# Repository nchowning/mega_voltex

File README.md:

# MEGA Voltex
An Arduino Mega 2560 Sound Voltex controller shield for use with [ACreal_IO](https://github.com/Nadeflore/ACreal_IO).

This is still SUPER early days. The plan is to solder components to this shield, desolder the USB connector & power connector from an Arduino Mega 2560, slap this bad boy on top of it, and design a 3D printed enclosure for it.

# Credit
- [mon's PocketVoltex](https://github.com/mon/PocketVoltex) - Rotary encoder footprint & model. mon has a ton of amazing projects and is a super nice guy!
- [kcswalter's Electronic CAD libraries](http://smisioto.no-ip.org/elettronica/kicad/kicad-en.htm) - Arduino Mega header. Lots of useful libraries, footprints, & models here!
- [KiCad's footprints](https://github.com/KiCad/kicad-footprints) - I modified a couple of their SW_Cherry MX1A footprints to add LED through-holes. I plan on submitting a PR upstream for this.

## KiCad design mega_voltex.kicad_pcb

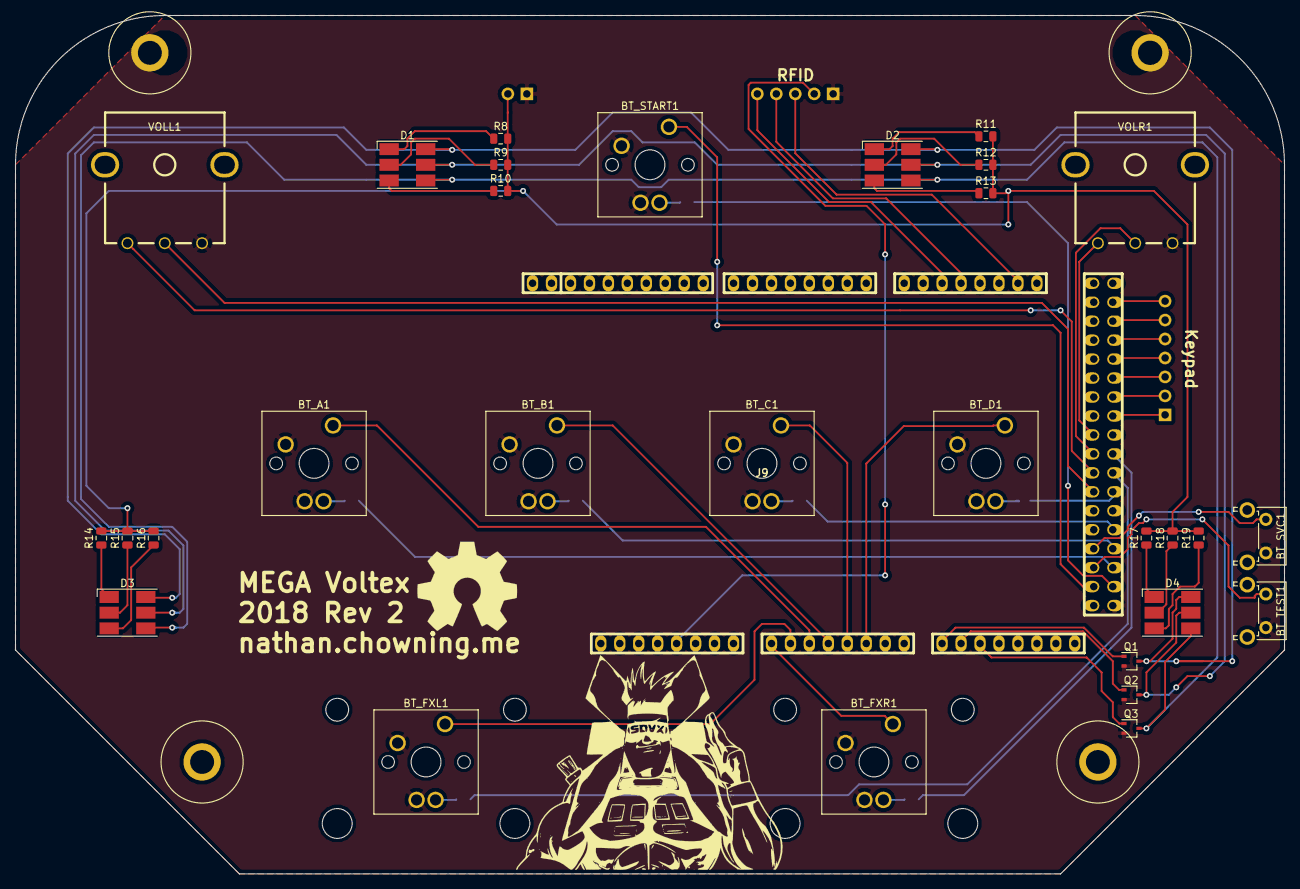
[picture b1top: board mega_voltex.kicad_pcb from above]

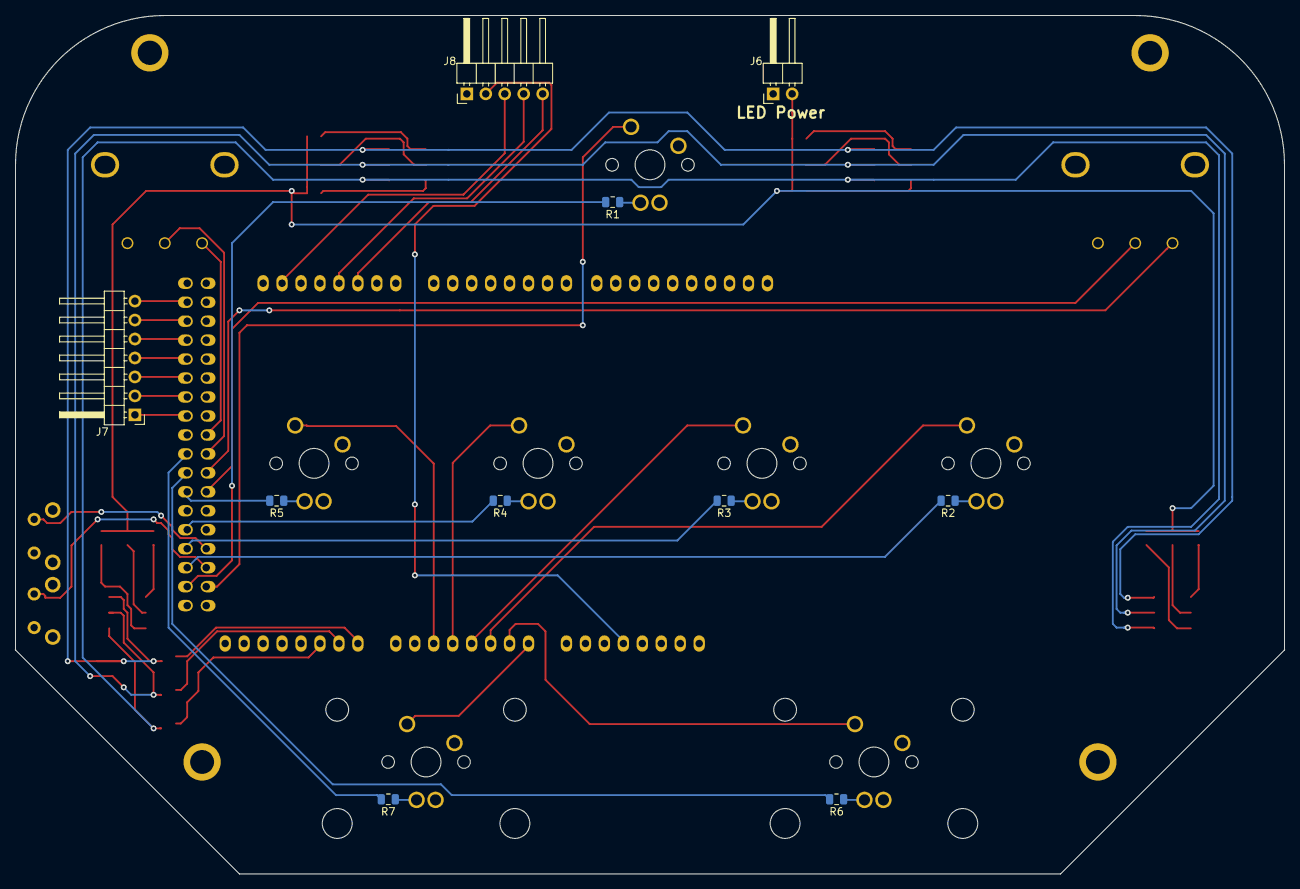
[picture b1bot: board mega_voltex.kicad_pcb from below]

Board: 2 copper layers, 170.0 x 115.0 mm, 44 parts (10 on the bottom side), 58 nets.

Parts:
BT_A1: SW_Push_LED; SW_Cherry_MX1A_1.00u_PCB
BT_B1: SW_Push_LED; SW_Cherry_MX1A_1.00u_PCB
BT_C1: SW_Push_LED; SW_Cherry_MX1A_1.00u_PCB
BT_D1: SW_Push_LED; SW_Cherry_MX1A_1.00u_PCB
BT_FXL1: SW_Push_LED; SW_Cherry_MX1A_2.00u_PCB
BT_FXR1: SW_Push_LED; SW_Cherry_MX1A_2.00u_PCB
BT_START1: SW_Push_LED; SW_Cherry_MX1A_1.00u_PCB
BT_SVC1: SW_Push; SW_Tactile_SPST_Angled_PTS645Vx58-2LFS
BT_TEST1: SW_Push; SW_Tactile_SPST_Angled_PTS645Vx58-2LFS
D1, D2, D3, D4: RGBLED_CREE_CLP6C; LED_RGB_Cree-PLCC-6_6x5mm_P2.1mm
J6: HEADER_2; PinHeader_1x02_P2.54mm_Horizontal
J7: HEADER_7; PinHeader_1x07_P2.54mm_Horizontal
J8: HEADER_5; PinHeader_1x05_P2.54mm_Horizontal
J9: Arduino_Mega_Header; arduino_mega_header
Mounting Hole: Banana_Jack_1Pin
Mounting Hole#2, Mounting Hole#3: Banana_Jack_1Pin
Q1, Q2, Q3: MMBT2222AWT1G; SOT-323_SC-70
R1, R2, R3, R4, R5, R6, R7, R8, R9, R10, R11, R12, R13, R14, R15, R16, R17, R18, R19: R_Small_US; R_0805_2012Metric
VOLL1: Rotary_Encoder; Encoder_Bourns_PEC16
VOLR1: Rotary_Encoder; Encoder_Bourns_PEC16

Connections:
5V: J8.2, J9.5
12V: J6.2, R8.2, R9.2, R10.2, R11.2, R12.2, R13.2, R14.2, R15.2, R16.2, R17.2, R18.2, R19.2
BT_A: BT_A1.1, J9.11
BT_B: BT_B1.1, J9.12
BT_C: BT_C1.1, J9.13
BT_D: BT_D1.1, J9.14
BT_FXL: BT_FXL1.1, J9.10
BT_FXR: BT_FXR1.1, J9.9
BT_START: BT_START1.1, J9.26
BT_SVC: BT_SVC1.1, J9.28
BT_TEST: BT_TEST1.1, J9.27
GND: BT_A1.2, BT_A1.3, BT_B1.2, BT_B1.3, BT_C1.2, BT_C1.3, BT_D1.2, BT_D1.3, BT_FXL1.2, BT_FXL1.3, BT_FXR1.2, BT_FXR1.3, BT_START1.2, BT_START1.3, BT_SVC1.2, BT_TEST1.2, J6.1, J8.1, J9.43, Q1.2, Q2.2, Q3.2, VOLL1.B, VOLR1.B
K1_1: J7.4, J9.56
K1_2: J7.3, J9.55
K1_3: J7.2, J9.54
K1_4: J7.1, J9.53
K1_A: J7.7, J9.59
K1_B: J7.6, J9.58
K1_C: J7.5, J9.57
LED6_B: D1.4, D2.4, D3.4, D4.4, Q3.3
LED6_G: D1.5, D2.5, D3.5, D4.5, Q2.3
LED6_R: D1.6, D2.6, D3.6, D4.6, Q1.3
LT_A: J9.45, R2.2
LT_B: J9.46, R3.2
LT_C: J9.47, R4.2
LT_D: J9.49, R5.2
LT_FXL: J9.50, R6.2
LT_FXR: J9.51, R7.2
LT_START: J9.44, R1.2
unnamed: BT_A1.4, R2.1
unnamed: BT_B1.4, R3.1
unnamed: BT_C1.4, R4.1
unnamed: BT_D1.4, R5.1
unnamed: BT_FXL1.4, R6.1
unnamed: BT_FXR1.4, R7.1
unnamed: BT_START1.4, R1.1
unnamed: D1.1, R8.1
unnamed: D1.2, R9.1
unnamed: D1.3, R10.1
unnamed: D2.1, R11.1
unnamed: D2.2, R12.1
unnamed: D2.3, R13.1
unnamed: D3.1, R14.1
unnamed: D3.2, R15.1
unnamed: D3.3, R16.1
unnamed: D4.1, R17.1
unnamed: D4.2, R18.1
unnamed: D4.3, R19.1
unnamed: J9.17, Q1.1
unnamed: J9.18, Q2.1
unnamed: J9.19, Q3.1
R1_DET: J8.3, J9.62
R1_RX: J8.4, J9.65
R1_TX: J8.5, J9.66
VOLL_A: J9.32, VOLL1.A
VOLL_B: J9.31, VOLL1.C
VOLR_A: J9.34, VOLR1.A
VOLR_B: J9.33, VOLR1.C

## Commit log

2018-11-01 Rearranged board, renamed module
2018-11-01 Added new footprints, updated schematic & PCB
2018-11-01 Added headers & resistors for LEDs
2018-11-01 Added library and changed reference to library
2018-11-01 Forgot to save for headers
2018-11-01 Lots of changes. PCB without LED1-5 headers is nearly complete
2018-11-09 Fixed some library/footprint difference issues with LEDs and transistors
2018-11-11 Added maxima silkscreen & moved top mounting holes
